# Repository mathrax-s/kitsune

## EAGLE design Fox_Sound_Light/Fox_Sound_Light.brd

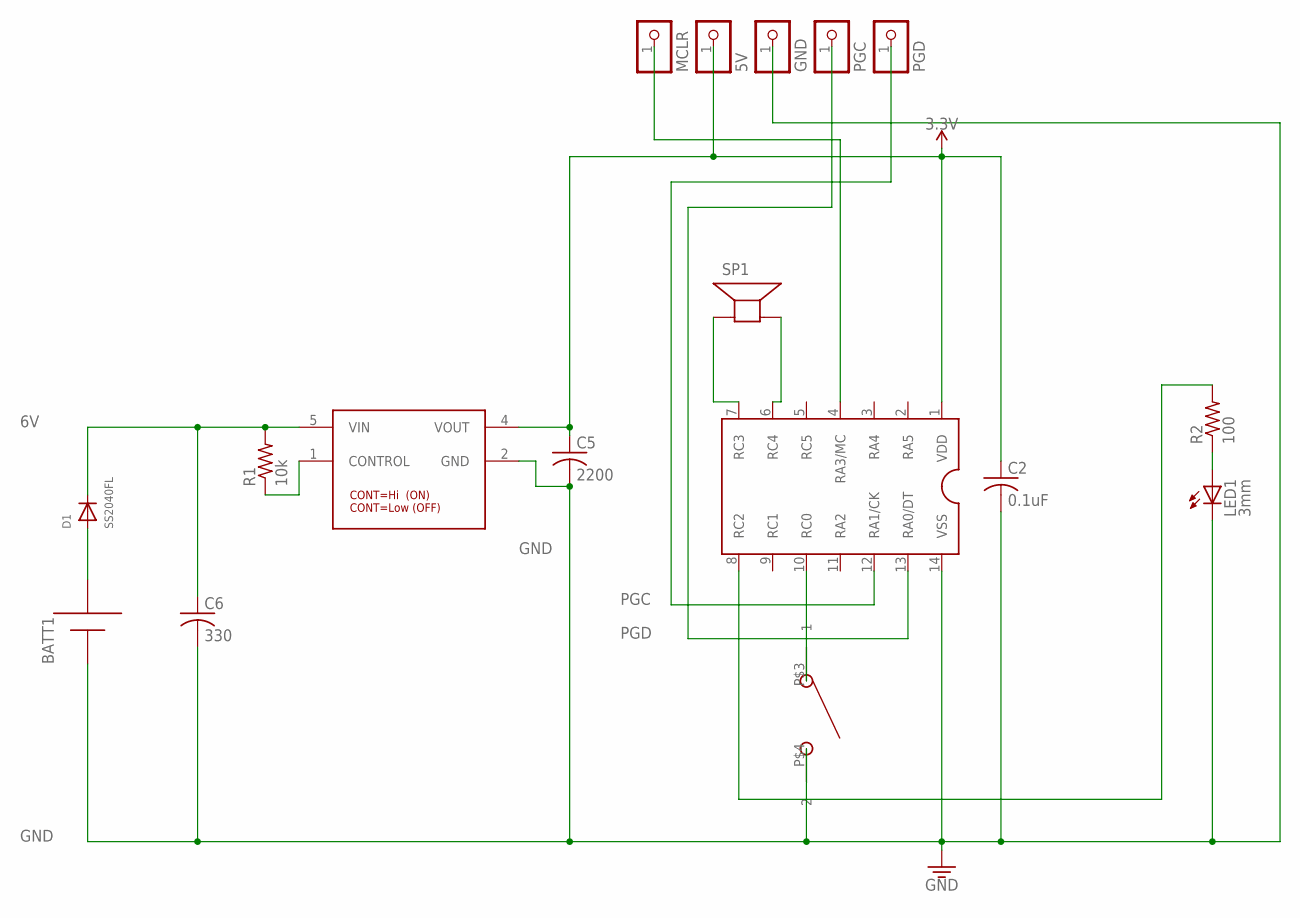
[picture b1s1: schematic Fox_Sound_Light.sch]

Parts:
BATT1: AAA_CR2032X2; CR2032X2
C2: 0.1uF; C0603
C5: 2200; C3216
C6: 330; C0603
D1: SS2040FL; SOD-123FL
JP1: MCLR; 1X01-CLEANBIG
JP2: 5V; 1X01-CLEANBIG
JP3: GND; 1X01-CLEANBIG
JP4: PGC; 1X01-CLEANBIG
JP5: PGD; 1X01-CLEANBIG
LED1: 3mm; LED3MM
NJM2884: NJM2884; NJM2884U1-33
R1: 10k; R0603
R2: 100; R0603
SP1: SPEAKER_MURATA; MURATA_PIEZO
U$1: LEAD-SWITCH_TILT; TILT-SWITCH
U$2: PIC16F1705SOP; 14PIN_SOP

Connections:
3.3V: C2.1, C5.1, JP2.1, NJM2884.4 (VOUT), U$2.1 (VDD)
6V: C6.1, D1.C, NJM2884.5 (VIN), R1.2
GND: BATT1.GND (-), C2.2, C5.2, C6.2, JP3.1, LED1.K (C), NJM2884.2 (GND), U$1.P$4 (2), U$2.14 (VSS)
unnamed: NJM2884.1 (CONTROL), R1.1
unnamed: LED1.A, R2.1
unnamed: U$1.P$3 (1), U$2.10 (RC0)
unnamed: SP1.2 (-), U$2.6 (RC4)
unnamed: SP1.1 (+), U$2.7 (RC3)
unnamed: R2.2, U$2.8 (RC2)
unnamed: JP1.1, U$2.4 (RA3/MC)
unnamed: BATT1.V (+), D1.A
PGC: JP5.1, U$2.12 (RA1/CK)
PGD: JP4.1, U$2.13 (RA0/DT)

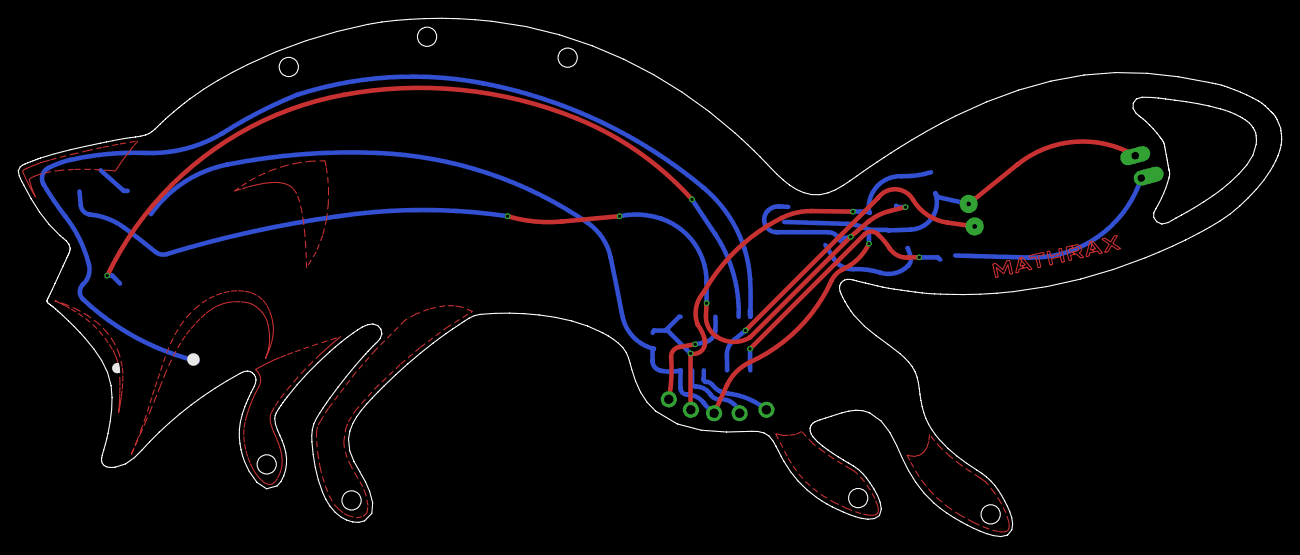
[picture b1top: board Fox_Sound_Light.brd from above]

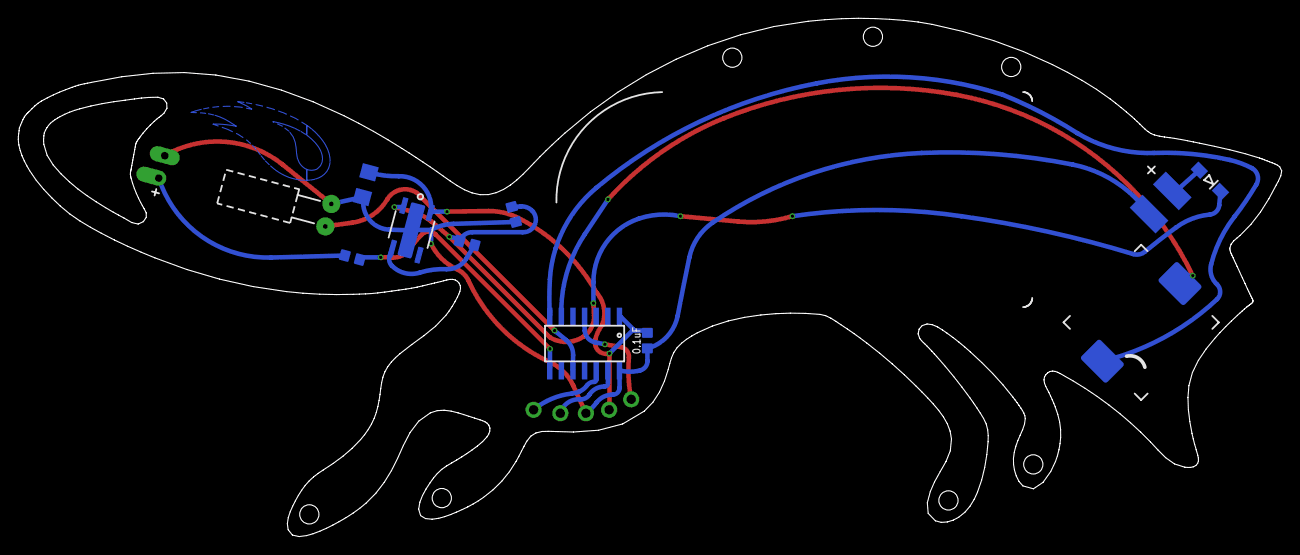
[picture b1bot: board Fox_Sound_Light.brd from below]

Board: 2 copper layers, 138.1 x 56.6 mm, 17 parts (12 on the bottom side), 13 nets.

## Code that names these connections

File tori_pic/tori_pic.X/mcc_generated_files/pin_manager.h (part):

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#define RA0_SetHigh()            do { LATAbits.LATA0 = 1; } while(0)
#define RA0_SetLow()             do { LATAbits.LATA0 = 0; } while(0)
#define RA0_Toggle()             do { LATAbits.LATA0 = ~LATAbits.LATA0; } while(0)
#define RA0_GetValue()              PORTAbits.RA0
#define RA0_SetDigitalInput()    do { TRISAbits.TRISA0 = 1; } while(0)
#define RA0_SetDigitalOutput()   do { TRISAbits.TRISA0 = 0; } while(0)
#define RA0_SetPullup()             do { WPUAbits.WPUA0 = 1; } while(0)
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#define RA1_SetHigh()            do { LATAbits.LATA1 = 1; } while(0)
#define RA1_SetLow()             do { LATAbits.LATA1 = 0; } while(0)
#define RA1_Toggle()             do { LATAbits.LATA1 = ~LATAbits.LATA1; } while(0)
#define RA1_GetValue()              PORTAbits.RA1
#define RA1_SetDigitalInput()    do { TRISAbits.TRISA1 = 1; } while(0)
#define RA1_SetDigitalOutput()   do { TRISAbits.TRISA1 = 0; } while(0)
#define RA1_SetPullup()             do { WPUAbits.WPUA1 = 1; } while(0)
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#define RC0_SetHigh()            do { LATCbits.LATC0 = 1; } while(0)
#define RC0_SetLow()             do { LATCbits.LATC0 = 0; } while(0)
#define RC0_Toggle()             do { LATCbits.LATC0 = ~LATCbits.LATC0; } while(0)
#define RC0_GetValue()              PORTCbits.RC0
#define RC0_SetDigitalInput()    do { TRISCbits.TRISC0 = 1; } while(0)
#define RC0_SetDigitalOutput()   do { TRISCbits.TRISC0 = 0; } while(0)
#define RC0_SetPullup()             do { WPUCbits.WPUC0 = 1; } while(0)
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#define RC2_SetHigh()            do { LATCbits.LATC2 = 1; } while(0)
#define RC2_SetLow()             do { LATCbits.LATC2 = 0; } while(0)
#define RC2_Toggle()             do { LATCbits.LATC2 = ~LATCbits.LATC2; } while(0)
#define RC2_GetValue()              PORTCbits.RC2
#define RC2_SetDigitalInput()    do { TRISCbits.TRISC2 = 1; } while(0)
#define RC2_SetDigitalOutput()   do { TRISCbits.TRISC2 = 0; } while(0)
#define RC2_SetPullup()             do { WPUCbits.WPUC2 = 1; } while(0)
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#define RC3_SetHigh()            do { LATCbits.LATC3 = 1; } while(0)
#define RC3_SetLow()             do { LATCbits.LATC3 = 0; } while(0)
#define RC3_Toggle()             do { LATCbits.LATC3 = ~LATCbits.LATC3; } while(0)
#define RC3_GetValue()              PORTCbits.RC3
#define RC3_SetDigitalInput()    do { TRISCbits.TRISC3 = 1; } while(0)
#define RC3_SetDigitalOutput()   do { TRISCbits.TRISC3 = 0; } while(0)
#define RC3_SetPullup()             do { WPUCbits.WPUC3 = 1; } while(0)
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#define RC4_SetHigh()            do { LATCbits.LATC4 = 1; } while(0)
#define RC4_SetLow()             do { LATCbits.LATC4 = 0; } while(0)
#define RC4_Toggle()             do { LATCbits.LATC4 = ~LATCbits.LATC4; } while(0)
#define RC4_GetValue()              PORTCbits.RC4
#define RC4_SetDigitalInput()    do { TRISCbits.TRISC4 = 1; } while(0)
#define RC4_SetDigitalOutput()   do { TRISCbits.TRISC4 = 0; } while(0)
#define RC4_SetPullup()             do { WPUCbits.WPUC4 = 1; } while(0)
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
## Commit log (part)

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2019-05-17 2019/05/17
2019-11-29 キツネも歩けば光る奏でる
2019-11-29 基板データ

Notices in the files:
tori_pic/tori_pic.X/mcc_generated_files/pin_manager.h:
(c) 2018 Microchip Technology Inc. and its subsidiaries.
